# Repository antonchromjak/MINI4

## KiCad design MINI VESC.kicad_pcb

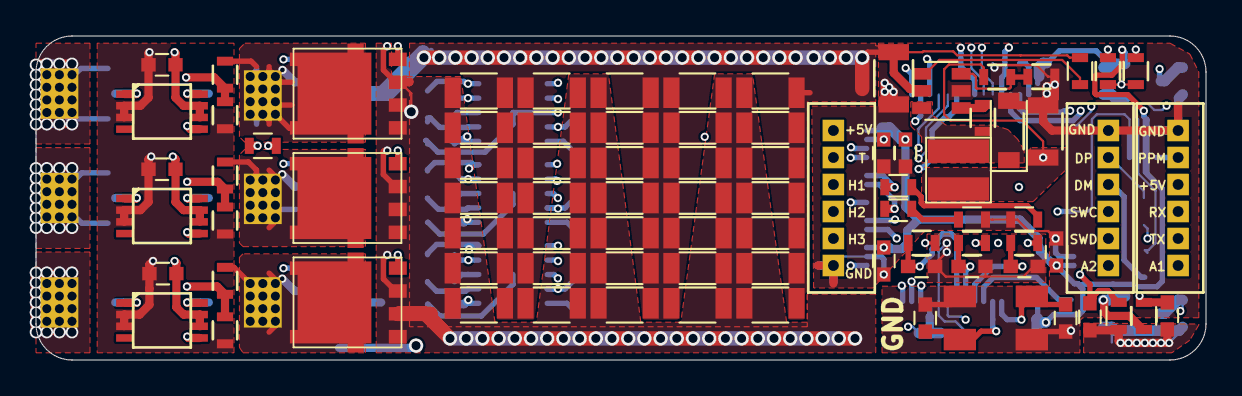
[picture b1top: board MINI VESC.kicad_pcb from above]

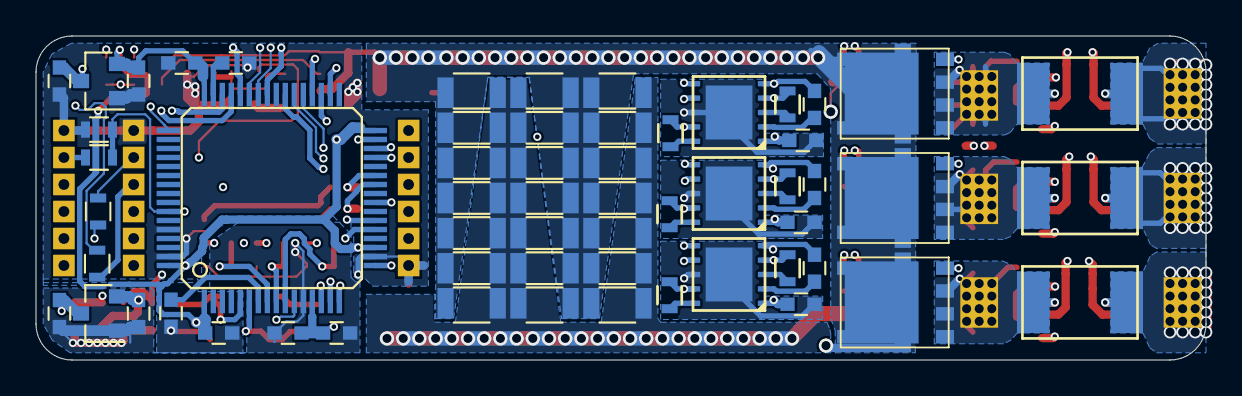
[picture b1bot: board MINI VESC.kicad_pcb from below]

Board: 4 copper layers, 65.0 x 18.0 mm, 151 parts (59 on the bottom side), 72 nets.

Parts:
C1, C2, C3: 220n; C_0603
C4, C5, C12, C13, C24, C25, C28, C32, C39, C48, C60, C61, C62, C63, C74, C75, C79, C82, C84, C85: 10u; R_1206
C6, C7, C8, C9, C10, C11, C17, C18, C19, C21, C22, C26, C27, C29, C77, C78, C86, C87, C88, C89, C90: 2u2; C_0603
C14, C15, C16: 4n7; C_0603
C20: 220nF; C_0603
C23: 220nF; R_0603
C30, C31: 10pF; C_0603
C33, C34, C35, C36, C37, C38, C40, C41, C42, C43, C44, C45, C46, C47, C49, C50, C51, C52, C53, C54, C55, C56, C57, C58, C59, C64, C65, C66, C67, C68, C69, C70, C71, C72, C73, C80, C81, C83: C; R_1206
C76: 100n; R_0603
D1: D_Schottky; D_SOD-123
D3, D4: LED; R_0603
L1: 22uH; WE-MAPI
P1, P2, P3, P4, P5, P6: CONN_1; prekov
P9, P10, P11: CONN_01X06; JST_ZH_1.5_6-Pin
Q1, Q2, Q3, Q4, Q5, Q6: Q_NMOS_GSD; DFN5
R1, R2, R3: RSENS; 2512Rv2
R4, R12, R14, R16: 25k5; R_0603
R5, R13, R15, R17: 2k2; R_0603
R6, R7, R8, R9, R10, R11: 7R5; R_0603
R18, R19, R20, R30: 100R; R_0603
R21: 510R; R_0603
R22: 8k; R_0603
R25, R27: 22R; R_0603
R28, R29: 220R; R_0603
R31, R33, R34: 10k; R_0603
R32: 10kNTC; R_0603
U1, U2, U3: LM5113; WSON10_
U4, U5, U6: AD8418; MSOP
U7: STM32F40X_LQFP64; lqfp64_pad_mod
U8: LMR16006; SOT-23-6
U9, U10: MCP1700; SOT-23
X1: CRYSTAL_SMD; 5x3.2KRISTALL

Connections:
+5V: C6.1, C7.1, C8.1, C25.2, C87.1, C89.1, L1.2, P9.1, P11.4, R22.1, U1.1, U2.1, U3.1, U9.3, U10.3
ADC_EXT1: P11.1, U7.21
ADC_EXT2: P10.1, U7.22
C1: C14.2, R18.2, U7.8
C2: C15.2, R19.2, U7.9
C3: C16.2, R20.2, U7.10
EN: R33.2, U8.4
HALL_1: P9.3, U7.37
HALL_2: P9.4, U7.38
HALL_3: P9.5, U7.39
HI1: U1.6, U7.41
HI2: U2.6, U7.42
HI3: U3.6, U7.43
I1: R18.1, U4.5
I2: R19.1, U5.5
I3: R20.1, U6.5
LED_GREEN: D3.2, U7.26
LED_RED: D4.2, U7.27
LI1: U1.7, U7.34
LI2: U2.7, U7.35
LI3: U3.7, U7.36
unnamed: C1.1, U1.2
unnamed: C2.1, U2.2
unnamed: C3.1, U3.2
unnamed: C17.2, U7.31
unnamed: C18.2, U7.47
unnamed: C20.2, U7.7
unnamed: C23.1, D1.1, L1.1, U8.6
unnamed: C23.2, U8.1
unnamed: C30.1, U7.5, X1.1
unnamed: C31.1, U7.6, X1.2
unnamed: C77.2, R31.2, R32.2, U7.17
unnamed: D3.1, R29.2
unnamed: D4.1, R28.2
unnamed: P1.1, R1.1, U4.1
unnamed: P2.1, R2.1, U5.1
unnamed: P3.1, R3.1, U6.1
unnamed: P10.4, R25.1
unnamed: P10.5, R27.1
unnamed: Q1.1, R6.1, U1.4
unnamed: Q2.1, R7.2, U1.9
unnamed: Q3.1, R8.1, U2.4
unnamed: Q4.1, R9.2, U2.9
unnamed: Q5.1, R10.1, U3.4
unnamed: Q6.1, R11.2, U3.9
unnamed: R6.2, U1.3
unnamed: R7.1, U1.10
unnamed: R8.2, U2.3
unnamed: R9.1, U2.10
unnamed: R10.2, U3.3
unnamed: R11.1, U3.10
unnamed: R21.2, R22.2, U8.3
RX: P11.3, U7.30
SENS_1: R12.1, R13.2, U7.14
SENS_2: R14.1, R15.2, U7.15
SENS_3: R16.1, R17.2, U7.16
SENS_SUPPLY: R4.2, R5.2, U7.11
SERVO: C76.2, R30.2, U7.58
SH1: C1.2, P4.1, Q1.2, Q2.3, R1.2, R12.2, U1.5, U4.8
SH2: C2.2, P5.1, Q3.2, Q4.3, R2.2, R14.2, U2.5, U5.8
SH3: C3.2, P6.1, Q5.2, Q6.3, R3.2, R16.2, U3.5, U6.8
SWCLK: P10.3, U7.49
SWDIO: P10.2, U7.46
TEMP_MOTOR: C78.2, P9.2, R34.2, U7.24
TX: P11.2, U7.29
USB-DM: R25.2, U7.44
USB-DP: R27.2, U7.45
VAA: C9.2, C10.2, C11.2, C19.1, C86.1, C90.1, R32.1, R34.1, U4.6, U4.7, U5.6, U5.7, U6.6, U6.7, U7.13, U10.2
VCC: C21.1, C22.1, C26.1, C27.1, C29.1, C88.1, U7.1, U7.19, U7.32, U7.48, U7.64, U9.2
VDD: C4.1, C5.1, C12.1, C13.1, C24.2, C28.1, C32.1, C33.1, C34.1, C35.1, C36.1, C37.1, C38.1, C39.1, C40.1, C41.1, C42.1, C43.1, C44.1, C45.1, C46.1, C47.1, C48.1, C49.1, C50.1, C51.1, C52.1, C53.1, C54.1, C55.1, C56.1, C57.1, C58.1, C59.1, C60.1, C61.1, C62.1, C63.1, C64.1, C65.1, C66.1, C67.1, C68.1, C69.1, C70.1, C71.1, C72.1, C73.1, C74.1, C75.1, C79.1, C80.1, C81.1, C82.1, C83.1, C84.1, C85.1, Q1.3, Q3.3, Q5.3, R4.1, R33.1, U8.5
VSS: C4.2, C5.2, C6.2, C7.2, C8.2, C9.1, C10.1, C11.1, C12.2, C13.2, C14.1, C15.1, C16.1, C17.1, C18.1, C19.2, C20.1, C21.2, C22.2, C24.1, C25.1, C26.2, C27.2, C28.2, C29.2, C30.2, C31.2, C32.2, C33.2, C34.2, C35.2, C36.2, C37.2, C38.2, C39.2, C40.2, C41.2, C42.2, C43.2, C44.2, C45.2, C46.2, C47.2, C48.2, C49.2, C50.2, C51.2, C52.2, C53.2, C54.2, C55.2, C56.2, C57.2, C58.2, C59.2, C60.2, C61.2, C62.2, C63.2, C64.2, C65.2, C66.2, C67.2, C68.2, C69.2, C70.2, C71.2, C72.2, C73.2, C74.2, C75.2, C76.1, C77.1, C78.1, C79.2, C80.2, C81.2, C82.2, C83.2, C84.2, C85.2, C86.2, C87.2, C88.2, C89.2, C90.2, D1.2, P9.6, P10.6, P11.6, Q2.2, Q4.2, Q6.2, R5.1, R13.1, R15.1, R17.1, R21.1, R28.1, R29.1, R31.1, U1.8, U2.8, U3.8, U4.2, U4.3, U5.2, U5.3, U6.2, U6.3, U7.12, U7.18, U7.60, U7.63, U8.2, U9.1, U10.1, X1.3
servoi: P11.5, R30.1

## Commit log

2017-11-26 photos
    photos
2017-11-26 3d images
2017-11-28 liberrr
2017-11-28 3d models
2017-12-12 new kicad port
    3d models change
2017-12-12 new kicad
2018-01-24 not much related pictures
2018-01-24 just schematic pdf
2018-01-24 bench
2018-04-19 gerbers
2018-08-08 update lib/sch to use kicad5 default library names/parts
